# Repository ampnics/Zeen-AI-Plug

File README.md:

# Zeen-AI-Plug (Zero Green AI Plug)

> An open-source, single-channel AI-powered smart plug built on ESP32-S3 with online (Sinric Pro / Google Home / Alexa) and offline timer-based control-designed and shared for the engineering community.

---

## 📺 Full Course-Hardware Design With AI Co-Pilot

This project is part of a complete open-source hardware design course on YouTube:

**▶️ [Hardware Design With AI Co-Pilot-Full Playlist](https://youtube.com/playlist?list=PLxgq6Jtu7shR8w3cHLHZtZtIrhJVOUqG1&si=Gfo0e48VRceQaZlR)**

The course covers the complete design journey-from schematic to PCB layout, firmware, and cloud integration.

---

---

## 📋 Table of Contents

- [Overview](#-overview)
- [Features](#-features)
- [Hardware Specifications](#-hardware-specifications)
- [System Architecture](#-system-architecture)
- [Operating Modes](#-operating-modes)
- [Repository Structure](#-repository-structure)
- [Getting Started](#-getting-started)
- [Firmware Setup](#-firmware-setup)
- [Cloud & Voice Assistant Integration](#-cloud--voice-assistant-integration)
- [Manufacturing](#-manufacturing)
- [Contributing](#-contributing)
- [License](#-license)

---

## 🔍 Overview

The **Zeen-AI-Plug (ZAP-01A)** is an open-source, single-channel smart plug designed for the engineering community. It combines an ESP32-S3 microcontroller with cloud-based AI voice assistants and a robust offline timer mode, making it functional even without an internet connection.

The board runs on **220VAC mains input**, converting it to **5V DC** via an onboard HLK-5M05 power supply module, and further to **3.3V** via an AMS1117-3.3 LDO - powering the ESP32-S3 and all peripherals.

---

## ✨ Features

- ✅ Single-channel relay control (SPDT)
- ✅ Online mode - Sinric Pro, Google Home, Amazon Alexa
- ✅ Offline mode - RTC-based (DS3231M) timer control
- ✅ USB-C (USB 2.0) for firmware flashing
- ✅ ESD protection on USB lines (USBLC6-2P6)
- ✅ Onboard RTC with battery backup (DS3231M + CH291-1220LF)
- ✅ Status LEDs - Network, Error, General indication
- ✅ Buzzer feedback (MLT-8530)
- ✅ 4x tactile switches for local control
- ✅ MOV surge protection (10D561K)
- ✅ Screw terminal output for load connection
- ✅ Fiducial markers for PCB assembly
- ✅ Fully open-source - Hardware + Firmware

---

## 🔧 Hardware Specifications

| Parameter | Details |
|---|---|
| Microcontroller | ESP32-S3-WROOM-1 |
| Input Voltage | 220V AC |
| Operating Voltage | 5V DC / 3.3V DC |
| Power Supply Module | HLK-5M05 (220VAC → 5VDC) |
| LDO Regulator | AMS1117-3.3 |
| Relay | SPDT — 1 Channel |
| RTC | DS3231M (I2C) |
| RTC Battery | CH291-1220LF (Coin Cell) |
| USB Connector | USB-C (USB 2.0) |
| ESD Protection | USBLC6-2P6 |
| Surge Protection | MOV 10D561K |
| Fuse | 500mA / 250V |
| Status LEDs | Red, Blue, Green |
| Buzzer | MLT-8530 |
| Switches | 4x Tactile + 1x Boot + 1x Reset |
| PCB Tool | KiCad 9.0.1 |
| Board Revision | Rev-v0.1.0A |

---

## 🏗️ System Architecture

```
220V AC Input
     │
     ▼
[F1 Fuse 500mA] ──→ [MOV RV1 Surge Protection]
     │
     ▼
[HLK-5M05] ──→ 5V DC
     │
     ├──→ [Relay K1 SPDT] ──→ Load Output (Screw Terminal J2)
     │
     └──→ [AMS1117-3.3] ──→ 3.3V DC
               │
               ├──→ [ESP32-S3-WROOM-1] ←→ WiFi / BLE
               ├──→ [DS3231M RTC] (I2C)
               ├──→ [Status LEDs]
               ├──→ [Buzzer MLT-8530]
               ├──→ [Tactile Switches x4]
               └──→ [USB-C] ──→ Firmware Flash / Serial Debug
```

---

## ⚙️ Operating Modes

### 🌐 Online Mode
- Connects to WiFi and syncs with **Sinric Pro** cloud platform
- Voice control via **Google Home** and **Amazon Alexa**
- Remote control from anywhere via smartphone app
- Real-time status sync across all platforms

### 📴 Offline Mode
- Fully functional without internet connection
- **DS3231M RTC** maintains accurate time even after power loss
- Timer-based scheduling stored locally
- Local switch control always active in both modes

---

## 📁 Repository Structure

```
Zeen-AI-Plug/
├── Docs/
│   ├── 1-Datasheet/           # Component datasheets
│   ├── 2-Images/              # PCB photos, product images
│   ├── 3-Pin-Mapping/         # ESP32-S3 pin mapping reference
│   └── 4-Testing-Note/        # Test procedures and results
├── Firmware/
│   ├── 1-Test-Code/           # Individual peripheral test sketches
│   └── 2-ZAP-01A-Firmware/    # Main production firmware
├── Hardware/
│   ├── 1-External-3D-Models/  # 3D models for KiCad
│   ├── 2-External-Libraries/  # Custom KiCad footprints & symbols
│   ├── 3-Manufacturing-Files/ # Gerbers, BOM, CPL
│   └── 4-ZAP-01A/             # KiCad project files
└── README.md
```

---

## 🚀 Getting Started

### Prerequisites
- [KiCad 9.0.1](https://www.kicad.org/) — for hardware files
- [Arduino IDE](https://www.arduino.cc/en/software) or [VS Code + ESP-IDF](https://docs.espressif.com/projects/esp-idf/en/latest/) — for firmware
- [Sinric Pro Account](https://sinric.pro/) — for cloud integration
- ESP32-S3 board support package installed in Arduino IDE

### Clone the Repository
```bash
git clone https://github.com/ampnics/Zeen-AI-Plug.git
cd Zeen-AI-Plug
```

---

## 💻 Firmware Setup

### 1. Install ESP32-S3 Board Support
In Arduino IDE → Preferences → add this URL:
```
https://raw.githubusercontent.com/espressif/arduino-esp32/gh-pages/package_esp32_index.json
```
Then: **Tools → Board → Boards Manager → search "esp32" → Install**

### 2. Install Required Libraries
```
Sinric Pro
ArduinoJson
WebSockets
NTPClient
RTClib (for DS3231)
```

### 3. Configure Credentials
Open `Firmware/2-ZAP-01A-Firmware/` and update:
```cpp
For WiFi press "SET" button for 10Sec for updating WiFi Credential via AP Mode
#define APP_KEY         "your_sinric_app_key"
#define APP_SECRET      "your_sinric_app_secret"
#define SWITCH_ID       "your_sinric_device_id"
```

### 4. Flash the Firmware
- Connect via **USB-C**
- Select Board: `ESP32S3 Dev Module`
- Press & hold **BOOT (SW1)** → tap **RESET (SW2)** → release BOOT
- Click **Upload**

---

## ☁️ Cloud & Voice Assistant Integration

### Sinric Pro Setup
1. Create account at [sinric.pro](https://sinric.pro)
2. Add new device → **Smart Plug**
3. Copy **App Key**, **App Secret**, **Device ID** into firmware
4. Flash firmware — device appears online automatically

### Google Home
1. Open Google Home app → **"+" → Set up device**
2. Search **"Sinric Pro"** → Link account
3. Your ZAP-01A plug appears as a controllable device
4. Say: *"Hey Google, turn on the plug"*

### Amazon Alexa
1. Open Alexa app → **Skills & Games**
2. Search **"Sinric Pro"** → Enable skill → Link account
3. Discover devices
4. Say: *"Alexa, turn on the plug"*

---

## 🏭 Manufacturing

Fabrication files are located in `Hardware/3-Manufacturing-Files/` and include:

- **Gerber files** - for PCB fabrication
- **BOM (Bill of Materials)** - component list with values and part numbers
- **CPL (Component Placement List)** - for SMT assembly

> ⚠️ **Safety Warning:** This board operates at **220V AC mains voltage**. Always ensure proper insulation and safety precautions during assembly and testing. Do not touch the board while connected to mains power.

---

## 🤝 Contributing

Contributions are welcome from the engineering community!

1. Fork the repository
2. Create your feature branch: `git checkout -b feature/your-feature`
3. Commit your changes: `git commit -m "feat: add your feature"`
4. Push to the branch: `git push origin feature/your-feature`
5. Open a **Pull Request**

**Commit message convention:**

| Prefix | Use for |
|---|---|
| `hw:` | Hardware / KiCad changes |
| `fw:` | Firmware changes |
| `docs:` | Documentation updates |
| `mfg:` | Manufacturing file updates |
| `fix:` | Bug fixes |

---

## 📄 License

This project is licensed under the **MIT License** — see the [LICENSE](LICENSE) file for details.

You are free to use, modify, and distribute this project for personal and commercial purposes with attribution.

---

## Designed By

**Md Ammar Maniyar** - [LinkedIn](https://www.linkedin.com/in/ammarece/)

## Sponsered By
**NextPCB** - [NextPCB](https://www.nextpcb.com/?code=Ampnics)

## Explore More
**Ampnics** - [Ampnics](https://www.ampnics.com)

*Engineered in India 🇮🇳*

---

## Support the Project

If this project helped you, consider:

- **Starring** this repository
- **Subscribing** to the [YouTube Channel](https://www.youtube.com/@ampnics)
- **Forking** and contributing back to the project

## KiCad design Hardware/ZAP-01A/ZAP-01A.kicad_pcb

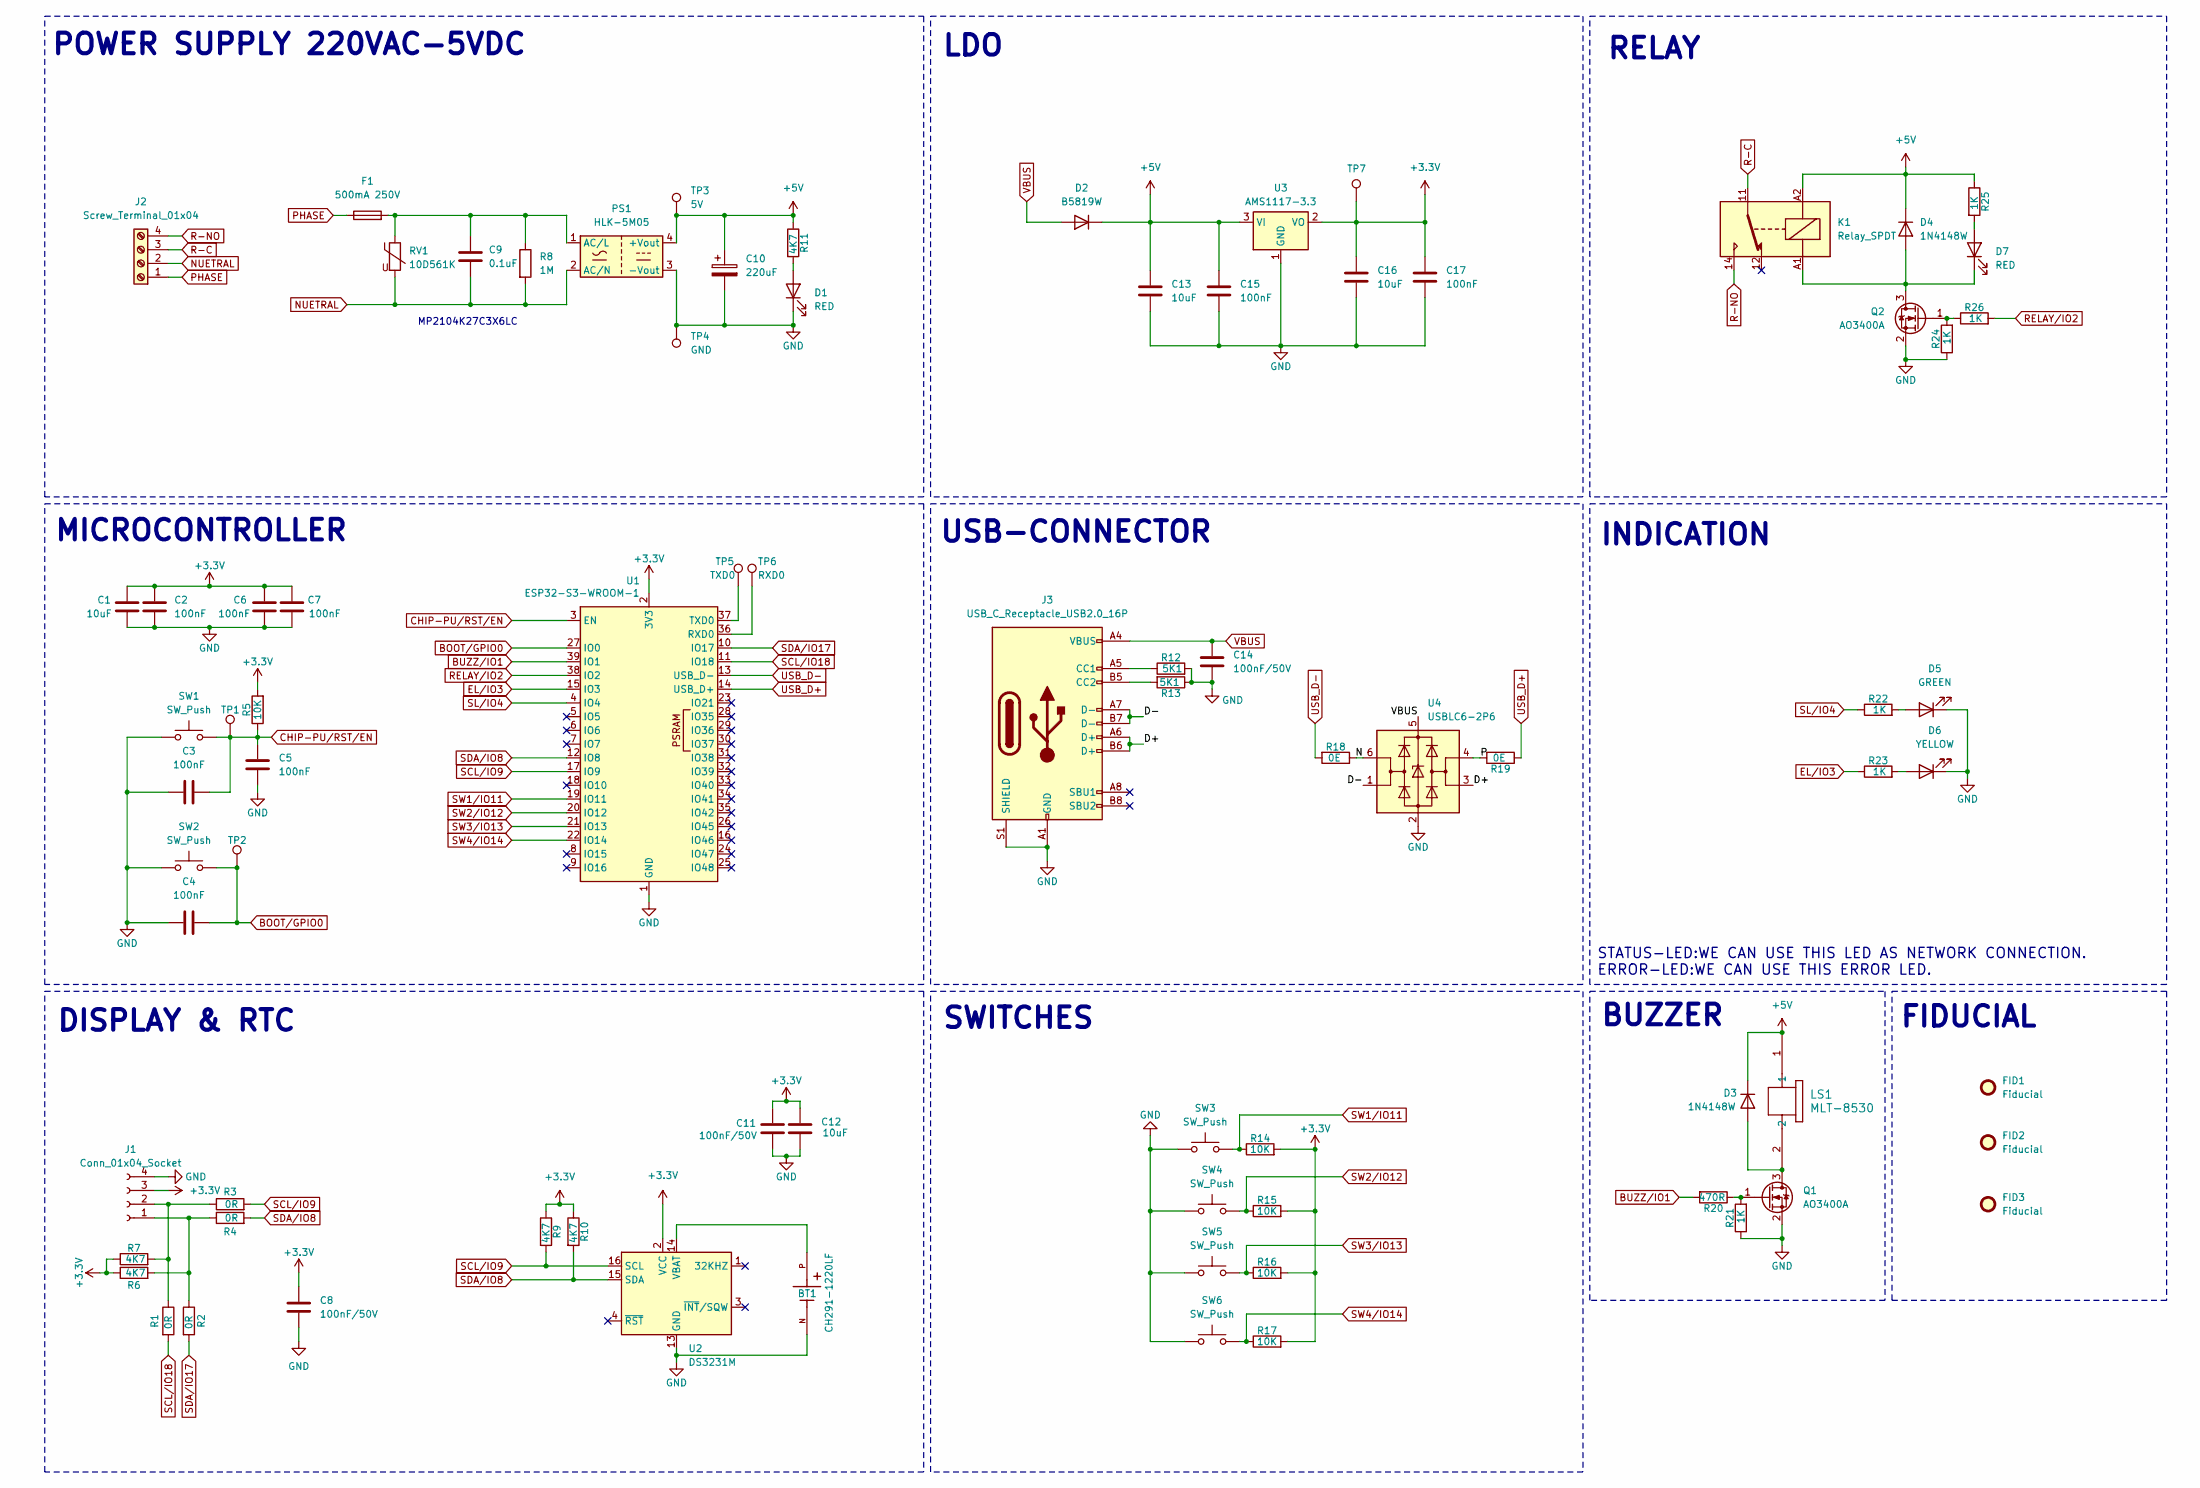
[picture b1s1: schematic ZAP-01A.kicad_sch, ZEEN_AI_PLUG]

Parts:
BT1: CH291-1220LF; BAT_CH291-1220LF; PARTREV A
C1, C12, C13, C16: 10uF; C_0805_2012Metric
C2, C3, C4, C5, C6, C7, C15, C17: 100nF; C_0603_1608Metric
C8, C11, C14: 100nF/50V; C_0603_1608Metric
C9: 0.1uF; C_Rect_L13.0mm_W6.0mm_P10.00mm_FKS3_FKP3_MKS4
C10: 220uF; CP_Elec_8x10
D1: RED; LED_D3.0mm
D2: B5819W; D_SOD-123
D3, D4: 1N4148W; D_SOD-123
D5: GREEN; LED_D3.0mm
D6: YELLOW; LED_D3.0mm
D7: RED; LED_0603_1608Metric
F1: 500mA 250V; Fuse_Littelfuse_395Series
FID1, FID2, FID3: Fiducial; Fiducial_0.75mm_Mask1.5mm
J1: Conn_01x04_Socket; PinSocket_1x04_P2.54mm_Vertical
J2: Screw_Terminal_01x04; TerminalBlock_bornier-4_P5.08mm
J3: USB_C_Receptacle_USB2.0_16P; USB_C_Receptacle_HCTL_HC-TYPE-C-16P-01A
K1: Relay_SPDT; Relay_SPDT_Hongfa_HF3F-L-xx-1ZL1T
LS1: MLT-8530; MLT-8530_JHE
PS1: HLK-5M05; Converter_ACDC_Hi-Link_HLK-5Mxx
Q1, Q2: AO3400A; SOT-23
R1, R2, R3, R4: 0R; R_0603_1608Metric
R5, R14, R15, R16, R17: 10K; R_0603_1608Metric
R6, R7, R9, R10, R11: 4K7; R_0603_1608Metric
R8: 1M; R_Axial_DIN0204_L3.6mm_D1.6mm_P7.62mm_Horizontal
R12, R13: 5K1; R_0603_1608Metric
R18, R19: 0E; R_0603_1608Metric
R20: 470R; R_0603_1608Metric
R21, R22, R23, R24, R25, R26: 1K; R_0603_1608Metric
RV1: 10D561K; RV_Disc_D12mm_W5.8mm_P7.5mm
SW1, SW3, SW4, SW5, SW6: SW_Push; SW_PUSH_6mm
SW2: SW_Push; SW_Push_SPST_NO_Alps_SKRK
TP1, TP2, TP7: 3.3V; TestPoint_Pad_D1.5mm
TP3: 5V; TestPoint_Pad_D1.5mm
TP4: GND; TestPoint_Pad_D1.5mm
TP5: TXD0; TestPoint_Pad_D1.5mm
TP6: RXD0; TestPoint_Pad_D1.5mm
U1: ESP32-S3-WROOM-1
U2: DS3231M; SOIC-16W_7.5x10.3mm_P1.27mm
U3: AMS1117-3.3; SOT-223-3_TabPin2
U4: USBLC6-2P6; SOT-666

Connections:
+3.3V: C1.1, C2.1, C6.1, C7.1, C8.1, C11.1, C12.1, C16.1, C17.1, J1.3, R5.2, R6.1, R7.1, R9.1, R10.1, R14.2, R15.2, R16.2, R17.2, TP7.1, U1.2 (3V3), U2.2 (VCC), U3.2 (VO)
+5V: C10.1, C13.1, C15.1, D2.1 (K), D3.1 (K), D4.1 (K), K1.A2, LS1.1, PS1.4 (+Vout), R11.1, R25.1, TP3.1, U3.3 (VI)
/D+: J3.A6 (D+), J3.B6 (D+), U4.3 (I/O2)
/D-: J3.A7 (D-), J3.B7 (D-), U4.1 (I/O1)
/N: R18.1, U4.6 (I/O1)
/P: R19.2, U4.4 (I/O2)
BOOT/GPIO0: C4.2, SW2.2, TP2.1, U1.27 (IO0)
BUZZ/IO1: R20.2, U1.39 (IO1)
CHIP-PU/RST/EN: C3.2, C5.1, R5.1, SW1.2, TP1.1, U1.3 (EN)
EL/IO3: R23.1, U1.15 (IO3)
GND: BT1.N, C1.2, C2.2, C3.1, C4.1, C5.2, C6.2, C7.2, C8.2, C10.2, C11.2, C12.2, C13.2, C14.2, C15.2, C16.2, C17.2, D1.1 (K), D5.1 (K), D6.1 (K), J1.4, J3.A1 (GND), J3.A12 (GND), J3.B1 (GND), J3.B12 (GND), J3.S1 (SHIELD), PS1.3 (-Vout), Q1.2 (S), Q2.2 (S), R12.2, R13.1, R21.1, R24.1, SW1.1, SW2.1, SW3.1, SW4.1, SW5.1, SW6.1, TP4.1, U1.1 (GND), U1.40 (GND), U1.41 (GND), U2.5 (GND), U2.6 (GND), U2.7 (GND), U2.8 (GND), U2.9 (GND), U2.10 (GND), U2.11 (GND), U2.12 (GND), U2.13 (GND), U3.1 (GND), U4.2 (GND)
unnamed: D1.2 (A), R11.2
unnamed: D3.2 (A), LS1.2, Q1.3 (D)
unnamed: D4.2 (A), D7.1 (K), K1.A1, Q2.3 (D)
unnamed: D5.2 (A), R22.2
unnamed: D6.2 (A), R23.2
unnamed: D7.2 (A), R25.2
unnamed: J1.1, R2.1, R4.1, R6.2
unnamed: J1.2, R1.1, R3.1, R7.2
unnamed: J3.A5 (CC1), R12.1
unnamed: J3.B5 (CC2), R13.2
unnamed: Q1.1 (G), R20.1, R21.2
unnamed: Q2.1 (G), R24.2, R26.1
unnamed: TP6.1, U1.36 (RXD0)
unnamed: TP5.1, U1.37 (TXD0)
unnamed: BT1.P, U2.14 (VBAT)
PHASE: F1.1, J2.1
R-C: J2.3, K1.11
R-NO: J2.4, K1.14
RELAY/IO2: R26.2, U1.38 (IO2)
SCL/IO9: R3.2, R9.2, U1.17 (IO9), U2.16 (SCL)
SCL/IO18: R1.2, U1.11 (IO18)
SDA/IO8: R4.2, R10.2, U1.12 (IO8), U2.15 (SDA)
SDA/IO17: R2.2, U1.10 (IO17)
SL/IO4: R22.1, U1.4 (IO4)
SW1/IO11: R14.1, SW3.2, U1.19 (IO11)
SW2/IO12: R15.1, SW4.2, U1.20 (IO12)
SW3/IO13: R16.1, SW5.2, U1.21 (IO13)
SW4/IO14: R17.1, SW6.2, U1.22 (IO14)
USB_D+: R19.1, U1.14 (USB_D+)
USB_D-: R18.2, U1.13 (USB_D-)
VBUS: C14.1, D2.2 (A), J3.A4 (VBUS), J3.A9 (VBUS), J3.B4 (VBUS), J3.B9 (VBUS), U4.5 (VBUS)

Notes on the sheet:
MICROCONTROLLER
BUZZER
DISPLAY & RTC
SWITCHES
INDICATION
MP2104K27C3X6LC
USB-CONNECTOR
RELAY
FIDUCIAL
LDO
POWER SUPPLY 220VAC-5VDC
STATUS-LED:WE CAN USE THIS LED AS NETWORK CONNECTION. ERROR-LED:WE CAN USE THIS ERROR LED.

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
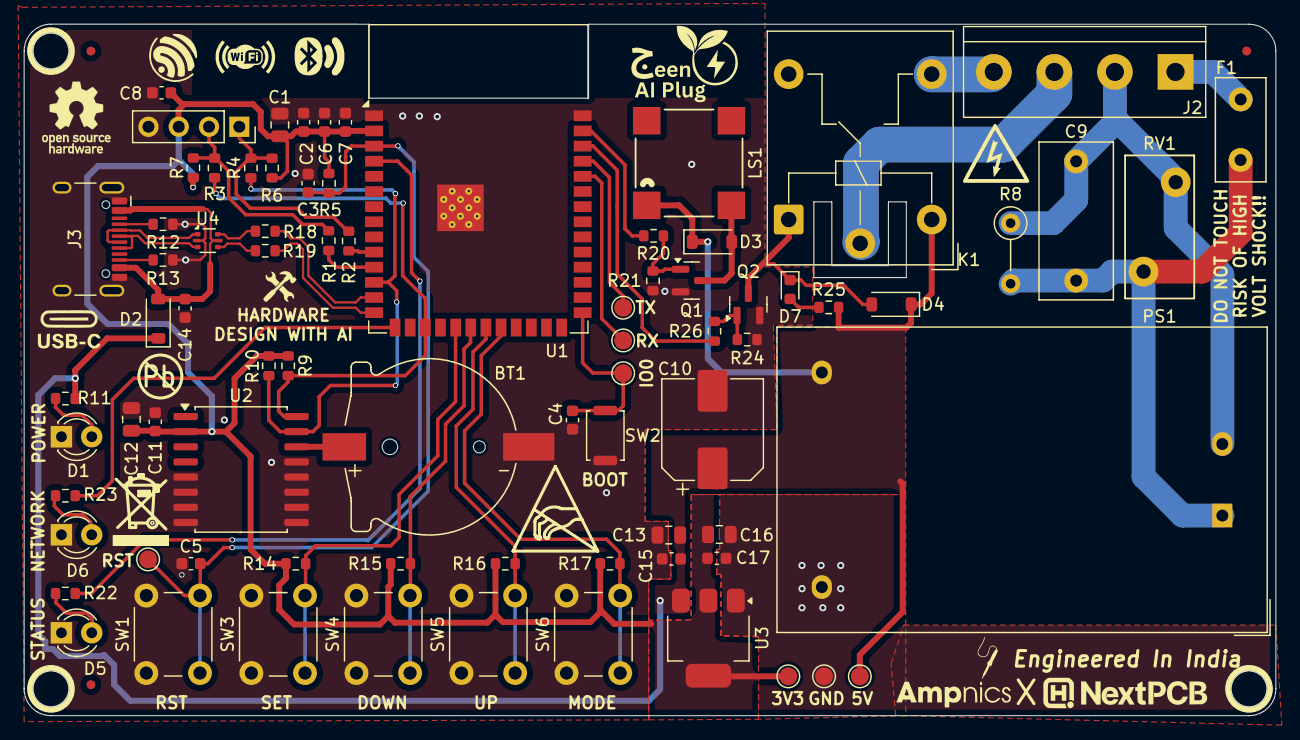
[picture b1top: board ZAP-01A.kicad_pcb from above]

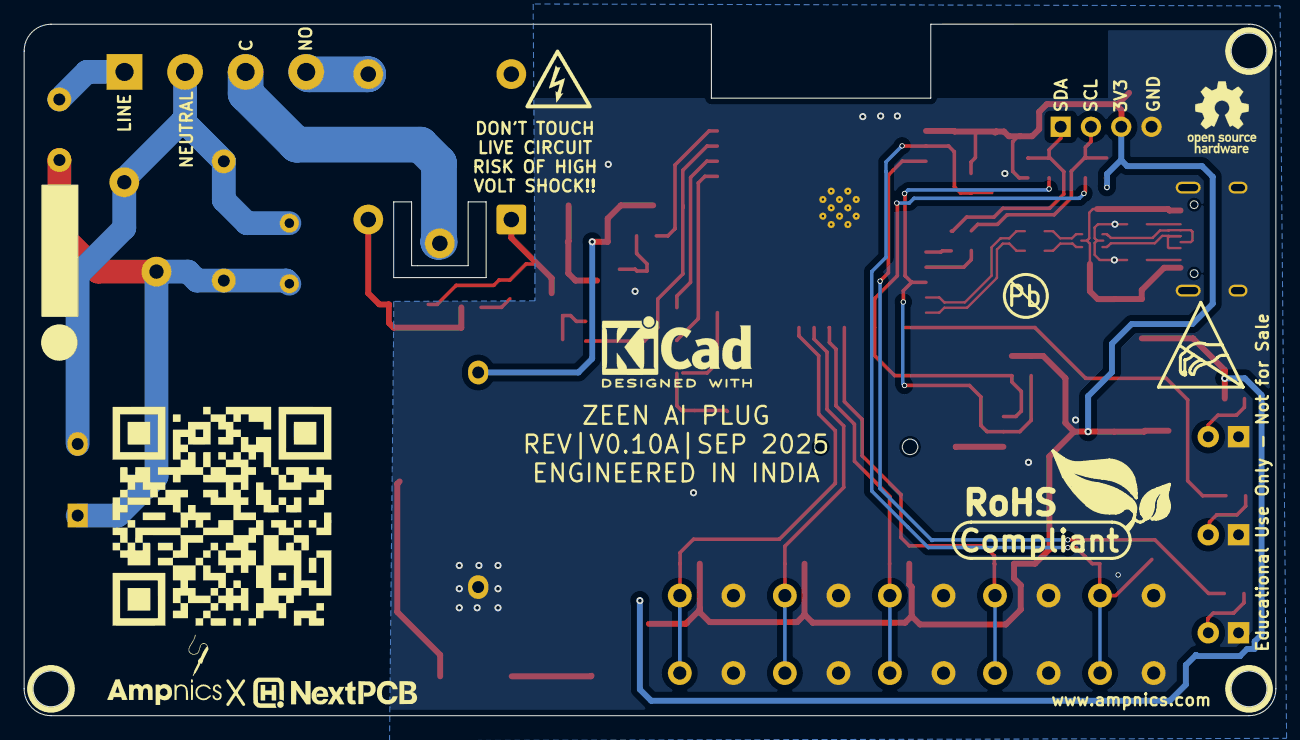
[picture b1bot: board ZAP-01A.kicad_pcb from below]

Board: 2 copper layers, 105.0 x 58.0 mm, 87 parts (3 on the bottom side), 44 nets.

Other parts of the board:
Sign-Antistatic: Val**; LOGO_ANTISTATIC_1
Sign-Antistatic#2: Val**; LOGO_ANTISTATIC_1
Sign-PbFree: LOGO_PBFREE
Sign-PbFree#2: LOGO_PBFREE
Sign-RecycleBin: LOGO_RECYCLEBIN_1
Sign-RoHS: Val**; LOGO_ROHS_1

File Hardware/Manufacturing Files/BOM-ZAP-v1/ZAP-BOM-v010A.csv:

S/N,Designator*,Quantity*,Manufacturer Part Number*,Package/Footprint,Description
1,BT1,1,XDCR-1220-006,CH291-1220LF:BAT_CH291-1220LF,CH291-1220LF
2,"C1,C12,C13,C16",4,CL21A106KAYNNNE,Capacitor_SMD:C_0805_2012Metric,10uF
3,"C2,C3,C4,C5,C6,C7,C15,C17",8,TCC0603X7R104K101CT,Capacitor_SMD:C_0603_1608Metric,100nF
4,"C8,C11,C14",3,TCC0603X7R104K101CT,Capacitor_SMD:C_0603_1608Metric,100nF/50V
5,C9,1,MP2104K27C3X6LC,Capacitor_THT:C_Rect_L13.0mm_W6.0mm_P10.00mm_FKS3_FKP3_MKS4,0.1uF
6,C10,1,RVT220UF25V67RV0093,Capacitor_SMD:CP_Elec_8x10,220uF
7,D1,1,XL-302SURD,LED_THT:LED_D3.0mm,RED
8,D2,1,B5819W,Diode_SMD:D_SOD-123,B5819W
9,"D3,D4",2,1N4148W,Diode_SMD:D_SOD-123,1N4148W
10,D5,1,XL-302UGD,LED_THT:LED_D3.0mm,GREEN
11,D6,1,XL-302UBD,LED_THT:LED_D3.0mm,BLUE
12,D7,1,D-060306B1/SS2/B1,LED_SMD:LED_0603_1608Metric,RED
13,F1,1,2009T500mA250V,Fuse:Fuse_Littelfuse_395Series,500mA 250V
14,J1,1,HS96L03W2C03,"0.96 128x64 SSD1315 I2C LCD, OLED, Graphic ROHS",Display
15,J2,1,DB128V-5.08-4P-GN-S,TerminalBlock:TerminalBlock_bornier-4_P5.08mm,Screw_Terminal_01x04
16,J3,1,KH-TYPE-C-16P,Connector_USB:USB_C_Receptacle_HCTL_HC-TYPE-C-16P-01A,USB_C_Receptacle_USB2.0_16P
17,K1,1,SRD-05VDC-SL-C,Relay_THT:Relay_SPDT_Hongfa_HF3F-L-xx-1ZL1T,Relay_SPDT
18,LS1,1,MLT-8530,ul_MLT-8530:MLT-8530_JHE,MLT-8530
19,PS1,1,HLK-5M05,Converter_ACDC:Converter_ACDC_Hi-Link_HLK-5Mxx,HLK-5M05
20,"Q1,Q2",2,AO3400A,Package_TO_SOT_SMD:SOT-23,AO3400A
21,"R1,R2,R3,R4",4,RC0603JR-070RL,Resistor_SMD:R_0603_1608Metric,0R
22,"R5,R14,R15,R16,R17",5,RC0603FR-0710KL,Resistor_SMD:R_0603_1608Metric,10K
23,"R6,R7,R9,R10,R11",5,RC0603FR-074K7L,Resistor_SMD:R_0603_1608Metric,4K7
24,R8,1,MF1/4W-1M±1%-OT52,Resistor_THT:R_Axial_DIN0204_L3.6mm_D1.6mm_P7.62mm_Horizontal,1M
25,"R12,R13",2,RC0603FR-075K1L,Resistor_SMD:R_0603_1608Metric,5K1
26,"R18,R19",2,RC0603JR-070RL,Resistor_SMD:R_0603_1608Metric,0E
27,R20,1,RC0603FR-07470RL,Resistor_SMD:R_0603_1608Metric,470R
28,"R21,R22,R23,R24,R25,R26",6,RC0603FR-071KL,Resistor_SMD:R_0603_1608Metric,1K
29,RV1,1,10D561K,Varistor:RV_Disc_D12mm_W5.8mm_P7.5mm,10D561K
30,"SW1,SW3,SW4,SW5,SW6",5,TC-1102-C-I-B,Button_Switch_THT:SW_PUSH_6mm,SW_Push
31,SW2,1,SKRKAHE020,Button_Switch_SMD:SW_Push_SPST_NO_Alps_SKRK,SW_Push
32,U1,1,ESP32-S3-WROOM-1-N8,RF_Module:ESP32-S3-WROOM-1,ESP32-S3-WROOM-1
33,U2,1,DS3231SN#,Package_SO:SOIC-16W_7.5x10.3mm_P1.27mm,DS3231M
34,U3,1,AMS1117-3.3,Package_TO_SOT_SMD:SOT-223-3_TabPin2,AMS1117-3.3
35,U4,1,USBLC6-2P6,Package_TO_SOT_SMD:SOT-666,USBLC6-2P6

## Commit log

2026-03-06 Initial release: Zeen-AI-Plug
2026-03-06 Initialize README for Zeen-AI-Plug project
    Add detailed project overview, features, specifications, and setup instructions for Zeen-AI-Plug.
2026-03-06 README.md
    Corrected the link formatting for Md Ammar Maniyar.
2026-03-06 README.md
